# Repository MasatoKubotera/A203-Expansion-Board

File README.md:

<html lang="en">

<head>
    <meta charset="uft-8">
    <meta name="author" content="Masato Kubotera">
    <meta name="description" content="">
</head>

<body>
    <p><strong>This product is currently under development!</strong></p>
    <h1>A203 V2 Expansion Board</h1>
        <p>
            This product is a board that expands the functions of the A203 (Version 2) carrier board manufactured by Seeed Stuido, developed for the SUSTAINA-OP<sup>TM</sup>. Several modules developed for SUSTAINA-OP<sup>TM</sup> can be attached/connected to this board and used by connecting to the Multifunctional Port and USB Port on the carrier board. In addition, the USB 2.0 High Speed(480MHz) 3-Port Hub is installed for further expandability.
        </p>
    <h2>Features Rev. 1</h2>
        <p>
            <table>
                <tr>
                    <th>Top Surface of PCB</th>
                    <th>Bottom Surface of PCB</th>
                    <th>Assembled Electronic Components</th>
                </tr>
                <tr>
                    <td></td>
                    <td></td>
                    <td></td>
                </tr>
            </table>
        </p>
    <h3>PCB</h3>
        <p>
            <ul>
                <li>81.20mm x 46.40mm PCB layout</li>
                The shape of the connector does not interfere with the connectors on the A203 V2.
                <li>Two types of USB-HUB Upstream Ports</li>
                    <ul>
                        <li>0.5mm pitch 20P ZIF Connector</li>
                        Compliant with W11: 20PIN(USB 3.0 ZIF) on the A203 V2.
                        <li>USB Mini-B Connector (Optional)</li>
                    </ul>
                <li>2 x USB 2.0 Type-A USB-HUB Downstream Ports</li>
                <li>1 x <a href="https://github.com/SUSTAINA-OP/ICM-42688-P-Module">SUSTAINA-OP/ICM-42688-P-Module</a> Attachment Port</li>
                The I/F with A203V2 can be selected from the following using the shortlands on the product.
                <ul>
                    <li>SPI </li>
                    <li>I2C: Selectable slave address 0x68/0x69</li>
                </ul>
                <li>1 x <a href="https://github.com/SUSTAINA-OP/USB-to-Quad-RS-485-Conv-Module">SUSTAINA-OP/USB-to-Quad-RS-485-Conv-Module</a> Attachment Port</li>
                <li>14 x LED Indicators</li>
                <li>
                    1 x Port for Connection to <a href="https://github.com/SUSTAINA-OP/SUSTAINA-Core-Board">SUSTAINA-OP/SUSTAINA-Core-Board</a>
                    <ul>
                        <li>2 x 7 Pin Flat Cable Connector (MIL Standard Connector)
                            <ul>
                                <li><strong>2 x 3V3</strong>: 3.3 V Power Supply</li>
                                <li><strong>SCL</strong>: I2C Serial Clock</li>
                                <li><strong>SDA</strong>: I2C Serial Data</li>
                                <li><strong>A-DP</strong>: RS-485 Data Signal Plus of CH-A</li>
                                <li><strong>A-DM</strong>: RS-485 Data Signal Minus of CH-A</li>
                                <li><strong>B-DP</strong>: RS-485 Data Signal Plus of CH-B</li>
                                <li><strong>B-DM</strong>: RS-485 Data Signal Minus of CH-B</li>
                                <li><strong>C-DP</strong>: RS-485 Data Signal Plus of CH-C</li>
                                <li><strong>C-DM</strong>: RS-485 Data Signal Minus of CH-C</li>
                                <li><strong>D-DP</strong>: RS-485 Data Signal Plus of CH-D</li>
                                <li><strong>D-DM</strong>: RS-485 Data Signal Minus of CH-D</li>
                                <li><strong>2 x GND</strong>: Common Ground</li>
                            </ul>
                        </li>
                    </ul>
                </li>
            </ul>
        </p>
    <h2>Development Environments</h2>
    <p>
        This product is designed with the following software.
            <ul>
                <li><a href="https://www.autodesk.com/products/eagle/overview">Autodesk Eagle 9.6.2</a></li>
            </ul>
    </p>
    <h2>Repository Contents</h2>
        <p>
            <dl>
                <dt><a href="/images">\images</a></dt>
                <dd>PCB preview images and capture of design screen</dd>
                <dt><a href="/libraries">\libraries</a></dt>
                <dd>Libraries used in Autodesk Eagle design</dd>
                <dt><a href="/pcb_order">\pcb_order</a> </dt>
                <dd>Gerber data and documentation for ordering PCB</dd>
                <dt><a href="/schematic.pdf">schematic.pdf</a></dt>
                <dd>Circuit diagram of this product</dd>
                <dt>*.brd</dt>
                <dd>Board wiring design file by Autodesk Eagle</dd>
                <dt>*.sch</dt>
                <dd>Circuit diagram design file by Autodesk Eagle</dd>
                <dt><a href="/.gitignore">.gitignore</a></dt>
                <dd>A file that tells Git not to track a particular file</dd>            <dt><a href="/LICENSE">LICENSE</a></dt>
                <dd>License to use this product</dd>
            </dl>
        </p>
    <h2>Documentation</h2>
        <p>
            The following documents are available for this product.
            <ul>
                <li><a href="/pcb_order/README.md">\pcb_order\README.md</a>: Information for ordering the PCB or PCBA</li>
            </ul>
        </p>
    <h2>References</h2>
        
    <h2>Contact</h2>
        <p>
            If you have any questions, please contact the designer of this product, Masato Kubodera, by <a href="mailto:masato.kubotera@sustaina-op.com">e-mail</a>.<br>
            E-mail: <a href="mailto:masato.kubotera@sustaina-op.com">masato.kubotera@sustaina-op.com</a>
        </p>
    <h2>License Information</h2>
        <p>
            This product is open source. Please review the <a href="/LICENSE">LICENSE</a> for license information.<br>
            <br>
            This product by Masato Kubotera is licensed under a <a href="http://creativecommons.org/licenses/by-nc-sa/4.0/">Creative Commons Attribution-NonCommercial-ShareAlike 4.0 International License</a>.
        </p>
</body>
</html>

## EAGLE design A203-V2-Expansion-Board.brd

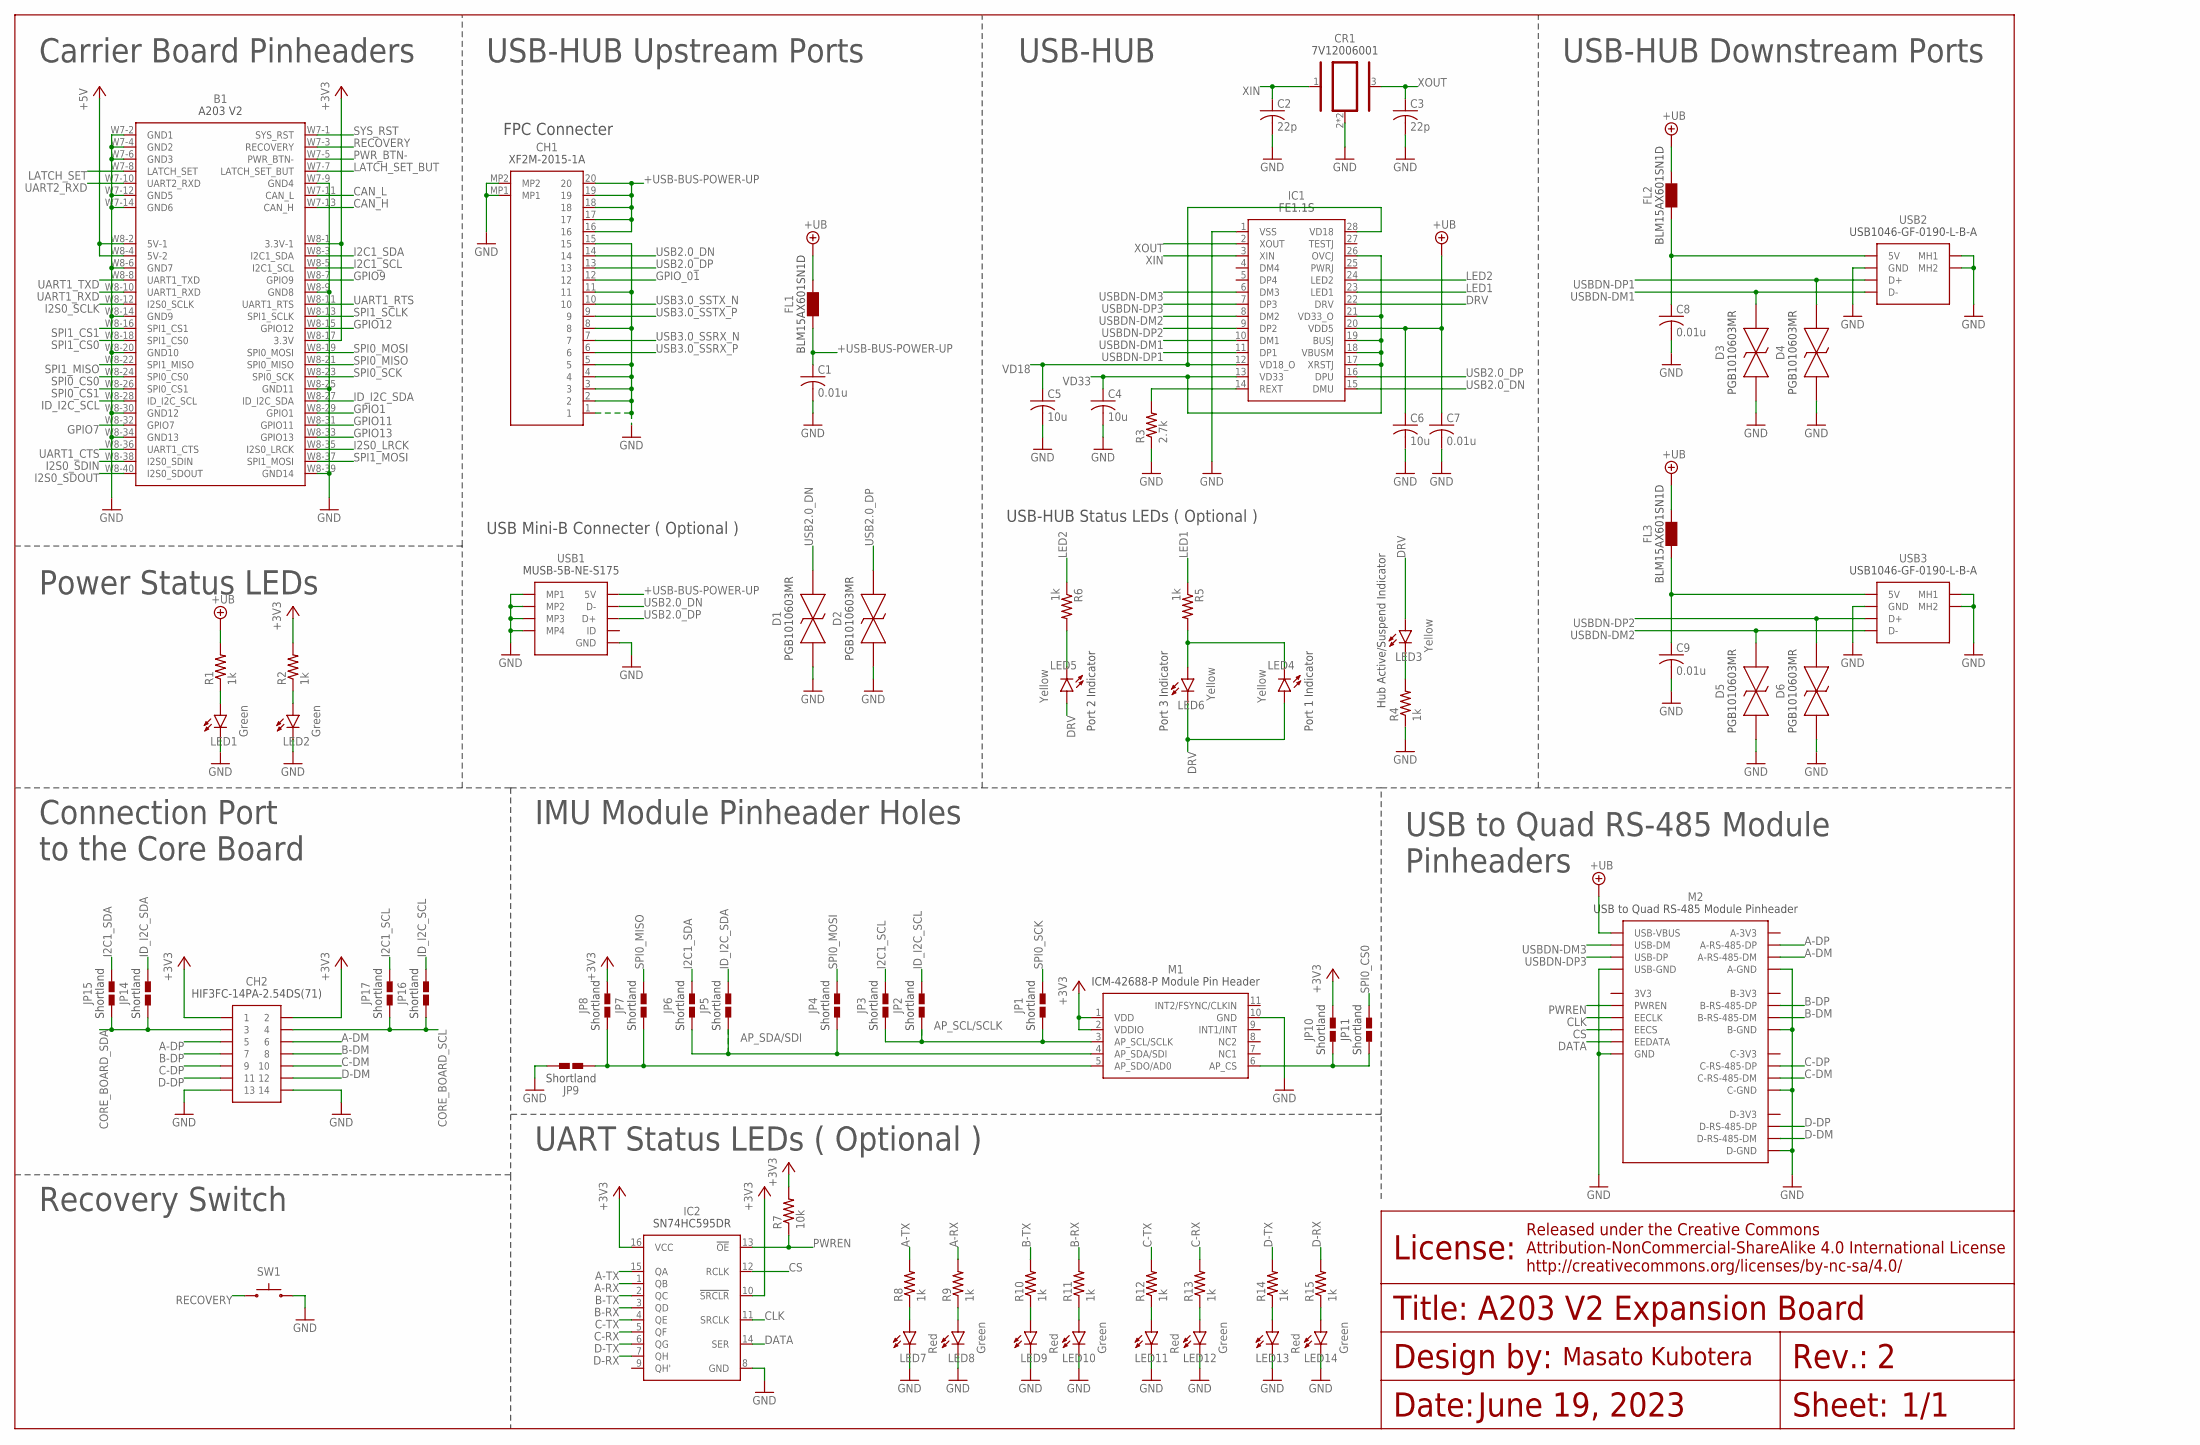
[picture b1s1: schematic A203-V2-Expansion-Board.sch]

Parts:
B1: SEEED_A207_V2; SEEED_A203_V2
C1, C7, C8, C9: 0.01u; C0603
C2, C3: 22p; C0603
C4, C5, C6: 10u; C0603
CH1: XF2M-2015-1A
CH2: HIF3FC-14PA-2.54DS(71)
CR1: 7V12006001
D1, D2, D3, D4, D5, D6: PGB1010603MR; 0603
FL1, FL2, FL3: BLM15AX601SN1D
IC1: FE1.1S
IC2: SN74HC595DR; SOIC-16
JP1, JP2, JP3, JP4, JP5, JP6, JP7, JP8, JP9, JP10, JP11, JP14, JP15, JP16, JP17: SHORTLAND
LED1, LED2, LED8, LED10, LED12, LED14: Green; SML0603
LED3, LED4, LED5, LED6: Yellow; SML0603
LED7, LED9, LED11, LED13: Red; SML0603
M1: ICM-42688-P-MODULE-PINHEADER
M2: USB-TO-QUAD-RS-485-CONV-MODULET-PLACE; USB-TO-QUAD-RS-485-CONV-MODULE-SILK
R1, R2, R4, R5, R6, R8, R9, R10, R11, R12, R13, R14, R15: 1k; R0603
R3: 2.7k; R0603
R7: 10k; R0603
SW1: SKRPACE010
USB1: MINI_USB_B_SMD
USB2, USB3: USB_A_X1_SMD

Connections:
+3V3: B1.W8-1 (3.3V-1), B1.W8-17 (3.3V), CH2.1, CH2.2, IC2.10 (!SRCLR), IC2.16 (VCC), JP8.2, JP10.2, M1.1 (VDD), M1.2 (VDDIO), R2.2, R7.2
+5V: B1.W8-2 (5V-1), B1.W8-4 (5V-2)
+UB: C6.1, C7.1, FL1.2, FL2.2, FL3.2, IC1.20 (VDD5), M2.USB-VBUS, R1.2
+USB-BUS-POWER-UP: C1.1, CH1.16, CH1.17, CH1.18, CH1.19, CH1.20, FL1.1, USB1.1 (5V)
+USB-BUS-POWER_DN1: C8.1, FL2.1, USB2.1 (5V)
+USB-BUS-POWER_DN2: C9.1, FL3.1, USB3.1 (5V)
A-DM: CH2.6, M2.A-RS-485-DM
A-DP: CH2.5, M2.A-RS-485-DP
A-RX: IC2.1 (QB), R9.2
A-TX: IC2.15 (QA), R8.2
AP_CS: JP10.1, JP11.1, M1.6 (AP_CS)
AP_SCL/SCLK: JP1.1, JP2.1, JP3.1, M1.3 (AP_SCL/SCLK)
AP_SDA/SDI: JP4.1, JP5.1, JP6.1, M1.4 (AP_SDA/SDI)
AP_SDO/ADO: JP7.1, JP8.1, JP9.1, M1.5 (AP_SDO/AD0)
B-DM: CH2.8, M2.B-RS-485-DM
B-DP: CH2.7, M2.B-RS-485-DP
B-RX: IC2.3 (QD), R11.2
B-TX: IC2.2 (QC), R10.2
C-DM: CH2.10, M2.C-RS-485-DM
C-DP: CH2.9, M2.C-RS-485-DP
C-RX: IC2.5 (QF), R13.2
C-TX: IC2.4 (QE), R12.2
CAN_H: B1.W7-13 (CAN_H)
CAN_L: B1.W7-11 (CAN_L)
CLK: IC2.11 (SRCLK), M2.EECLK
CORE_BOARD_SCL: CH2.4, JP16.1, JP17.1
CORE_BOARD_SDA: CH2.3, JP14.1, JP15.1
CS: IC2.12 (RCLK), M2.EECS
D-DM: CH2.12, M2.D-RS-485-DM
D-DP: CH2.11, M2.D-RS-485-DP
D-RX: IC2.7 (QH), R15.2
D-TX: IC2.6 (QG), R14.2
DATA: IC2.14 (SER), M2.EEDATA
DRV: IC1.22 (DRV), LED3.A, LED4.A, LED5.A, LED6.C
GND: B1.W7-2 (GND1), B1.W7-4 (GND2), B1.W7-6 (GND3), B1.W7-9 (GND4), B1.W7-12 (GND5), B1.W7-14 (GND6), B1.W8-6 (GND7), B1.W8-9 (GND8), B1.W8-14 (GND9), B1.W8-20 (GND10), B1.W8-25 (GND11), B1.W8-30 (GND12), B1.W8-34 (GND13), B1.W8-39 (GND14), C1.2, C2.2, C3.2, C4.2, C5.2, C6.2, C7.2, C8.2, C9.2, CH1.1, CH1.2, CH1.3, CH1.4, CH1.5, CH1.8, CH1.11, CH1.15, CH1.MP1, CH1.MP2, CH2.13, CH2.14, CR1.2, CR1.4, D1.1, D2.1, D3.1, D4.1, D5.1, D6.1, IC1.1 (VSS), IC2.8 (GND), JP9.2, LED1.C, LED2.C, LED7.C, LED8.C, LED9.C, LED10.C, LED11.C, LED12.C, LED13.C, LED14.C, M1.10 (GND), M2.A-GND, M2.B-GND, M2.C-GND, M2.D-GND, M2.GND1 (GND), M2.USB-GND, R3.1, R4.1, SW1.3 (2), SW1.4 (2), USB1.5 (GND), USB1.MP1, USB1.MP2, USB1.MP3, USB1.MP4, USB2.4 (GND), USB2.MH1, USB2.MH2, USB3.4 (GND), USB3.MH1, USB3.MH2
GPIO1: B1.W8-29 (GPIO1)
GPIO7: B1.W8-32 (GPIO7)
GPIO9: B1.W8-7 (GPIO9)
GPIO11: B1.W8-31 (GPIO11)
GPIO12: B1.W8-15 (GPIO12)
GPIO13: B1.W8-33 (GPIO13)
GPIO_01: CH1.12
I2C1_SCL: B1.W8-5 (I2C1_SCL), JP3.2, JP17.2
I2C1_SDA: B1.W8-3 (I2C1_SDA), JP6.2, JP15.2
I2S0_LRCK: B1.W8-35 (I2S0_LRCK)
I2S0_SCLK: B1.W8-12 (I2S0_SCLK)
I2S0_SDIN: B1.W8-38 (I2S0_SDIN)
I2S0_SDOUT: B1.W8-40 (I2S0_SDOUT)
ID_I2C_SCL: B1.W8-28 (ID_I2C_SCL), JP2.2, JP16.2
ID_I2C_SDA: B1.W8-27 (ID_I2C_SDA), JP5.2, JP14.2
LATCH_SET: B1.W7-8 (LATCH_SET)
LATCH_SET_BUT: B1.W7-7 (LATCH_SET_BUT)
LED1: IC1.23 (LED1), R5.1
LED2: IC1.24 (LED2), R6.1
LED-3V3: LED2.A, R2.1
LED-A-RX: LED8.A, R9.1
LED-A-TX: LED7.A, R8.1
LED-B-RX: LED10.A, R11.1
LED-B-TX: LED9.A, R10.1
LED-C-RX: LED12.A, R13.1
LED-C-TX: LED11.A, R12.1
LED-D-RX: LED14.A, R15.1
LED-D-TX: LED13.A, R14.1
LED-FE1.1S-DRV: LED3.C, R4.2
LED-FE1.1S-INDIVATOR1: LED4.C, LED6.A, R5.2
LED-FE1.1S-INDIVATOR2: LED5.C, R6.2
LED-UB: LED1.A, R1.1
PWREN: IC2.13 (!OE), M2.PWREN, R7.1
PWR_BTN-: B1.W7-5 (PWR_BTN-)
RECOVERY: B1.W7-3 (RECOVERY), SW1.1, SW1.2 (1)
REXT_FE1.1S: IC1.14 (REXT), R3.2
SPI0_CS0: B1.W8-24 (SPI0_CS0), JP11.2
SPI0_CS1: B1.W8-26 (SPI0_CS1)
SPI0_MISO: B1.W8-21 (SPI0_MISO), JP7.2
SPI0_MOSI: B1.W8-19 (SPI0_MOSI), JP4.2
SPI0_SCK: B1.W8-23 (SPI0_SCK), JP1.2
SPI1_CS0: B1.W8-18 (SPI1_CS0)
SPI1_CS1: B1.W8-16 (SPI1_CS1)
SPI1_MISO: B1.W8-22 (SPI1_MISO)
SPI1_MOSI: B1.W8-37 (SPI1_MOSI)
SPI1_SCLK: B1.W8-13 (SPI1_SCLK)
SYS_RST: B1.W7-1 (SYS_RST)
UART1_CTS: B1.W8-36 (UART1_CTS)
UART1_RTS: B1.W8-11 (UART1_RTS)
UART1_RXD: B1.W8-10 (UART1_RXD)
UART1_TXD: B1.W8-8 (UART1_TXD)
UART2_RXD: B1.W7-10 (UART2_RXD)
USB2.0_DN: CH1.14, D1.2, IC1.15 (DMU), USB1.2 (D-)
USB2.0_DP: CH1.13, D2.2, IC1.16 (DPU), USB1.3 (D+)
USB3.0_SSRX_N: CH1.7
USB3.0_SSRX_P: CH1.6
USB3.0_SSTX_N: CH1.10
USB3.0_SSTX_P: CH1.9
USBDN-DM1: D3.2, IC1.10 (DM1), USB2.2 (D-)
USBDN-DM2: D5.2, IC1.8 (DM2), USB3.2 (D-)
USBDN-DM3: IC1.6 (DM3), M2.USB-DM
USBDN-DP1: D4.2, IC1.11 (DP1), USB2.3 (D+)
USBDN-DP2: D6.2, IC1.9 (DP2), USB3.3 (D+)
USBDN-DP3: IC1.7 (DP3), M2.USB-DP
VD18: C5.1, IC1.12 (VD18_O), IC1.28 (VD18)
VD33: C4.1, IC1.13 (VD33), IC1.17 (XRSTJ), IC1.18 (VBUSM), IC1.19 (BUSJ), IC1.21 (VD33_O), IC1.26 (OVCJ)
XIN: C2.1, CR1.1, IC1.3 (XIN)
XOUT: C3.1, CR1.3, IC1.2 (XOUT)

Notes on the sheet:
Carrier Board Pinheaders
Power Status LEDs
UART Status LEDs ( Optional )
IMU Module Pinheader Holes
USB to Quad RS-485 Module Pinheaders
USB-HUB Upstream Ports
Connection Port to the Core Board
USB-HUB Downstream Ports
USB-HUB
1/1
June 19, 2023
A203 V2 Expansion Board
Hub Active/Suspend Indicator
Port 1 Indicator
Port 2 Indicator
Port 3 Indicator
USB Mini-B Connecter ( Optional )
FPC Connecter
USB-HUB Status LEDs ( Optional )
Recovery Switch

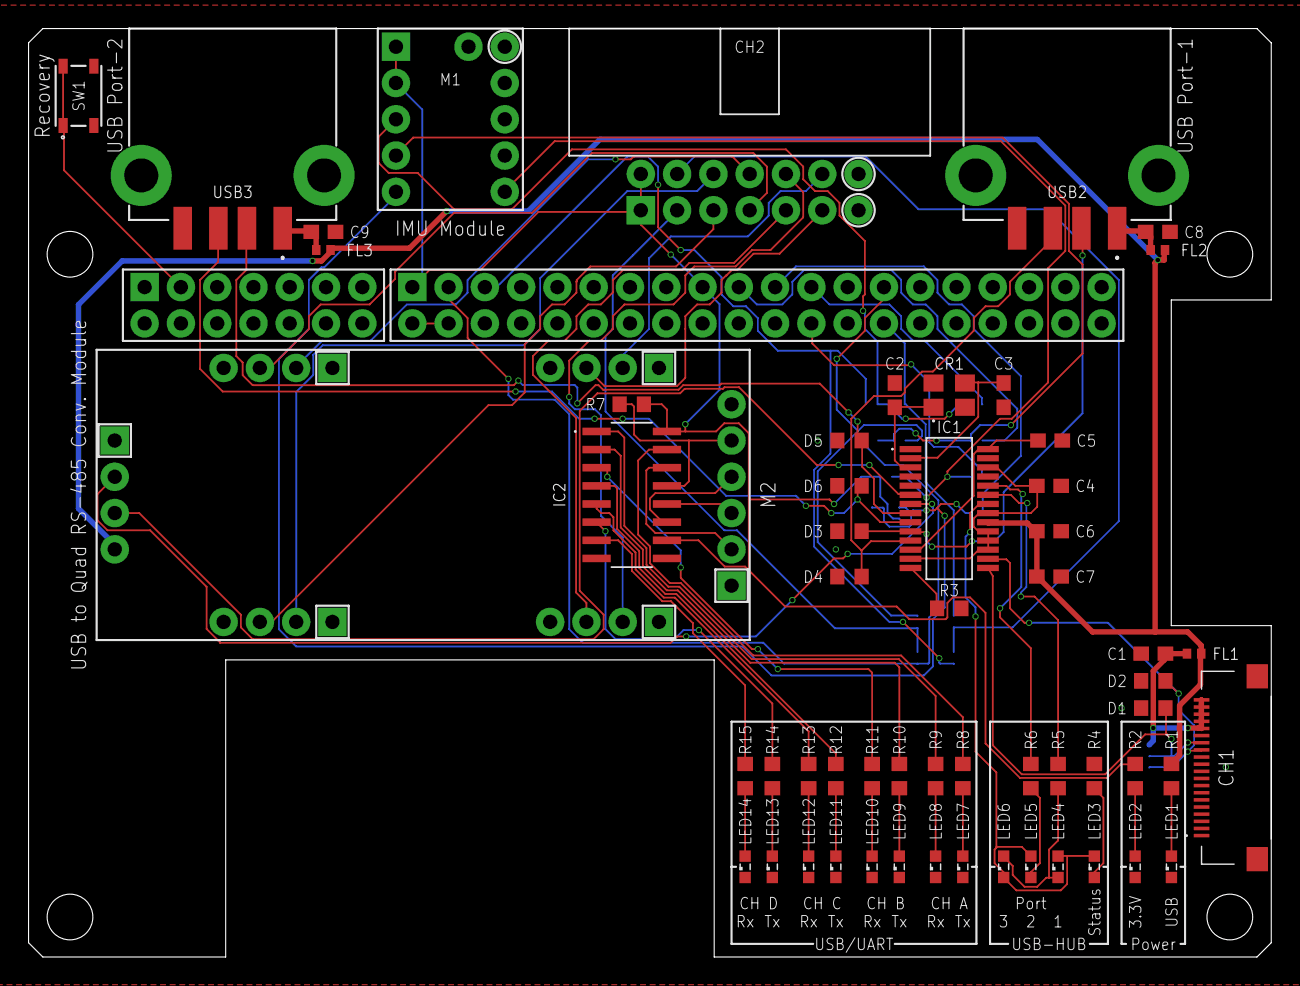
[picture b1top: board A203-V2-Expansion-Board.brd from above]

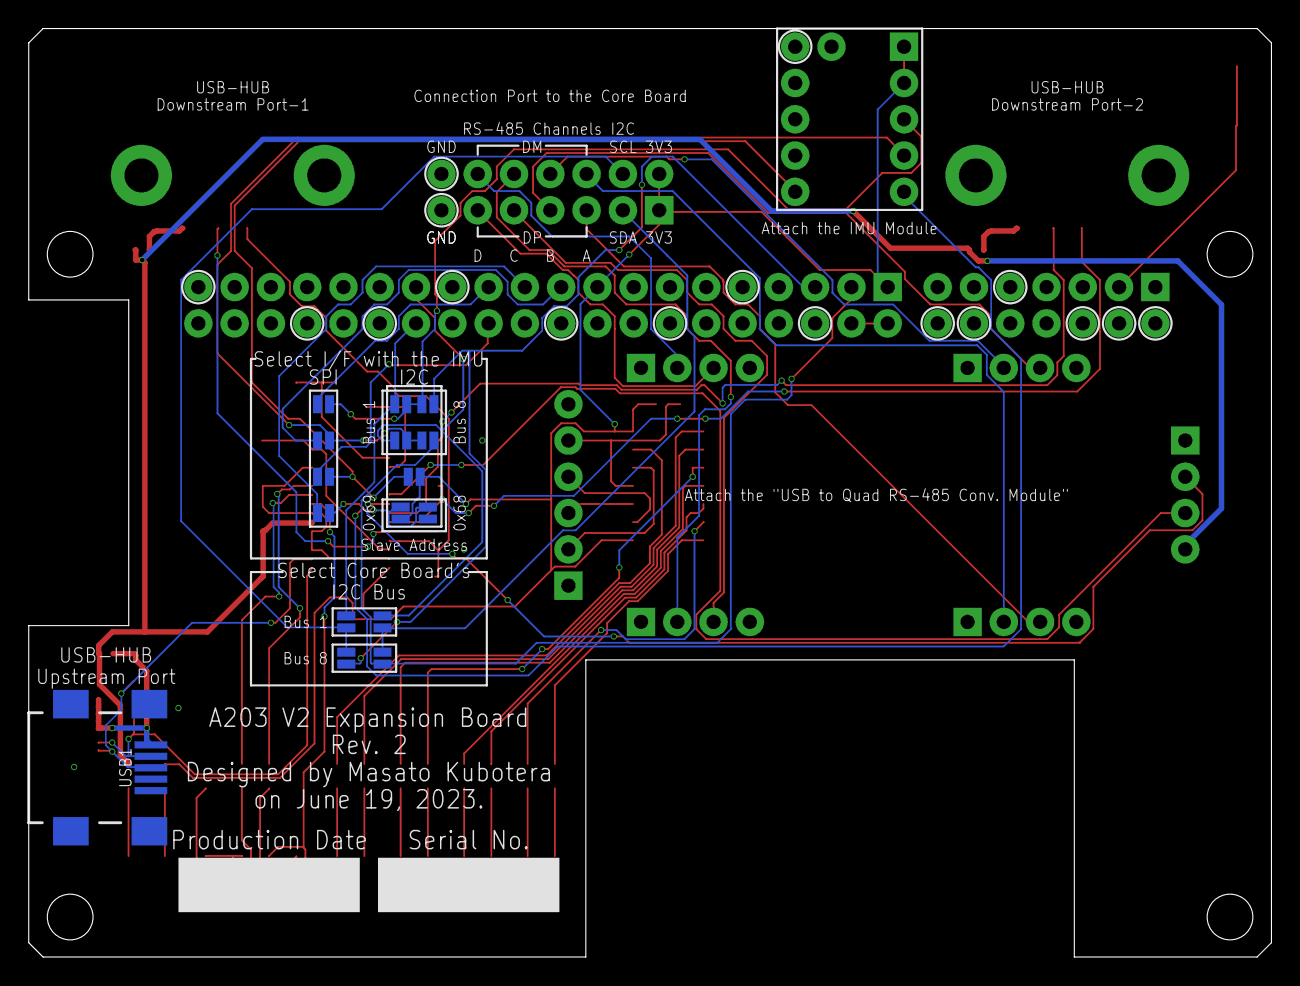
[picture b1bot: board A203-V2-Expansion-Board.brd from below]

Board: 2 copper layers, 87.0 x 65.0 mm, 74 parts (16 on the bottom side), 71 nets.

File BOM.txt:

Qty Value                                 Device                                Package                             Parts                                                                           Description                
4   0.01u                                 C-USC0603                             C0603                               C1, C7, C8, C9                                                                  CAPACITOR, American symbol 
1   10k                                   R-US_R0603                            R0603                               R7                                                                              RESISTOR, American symbol  
3   10u                                   C-USC0603                             C0603                               C4, C5, C6                                                                      CAPACITOR, American symbol 
13  1k                                    R-US_R0603                            R0603                               R1, R2, R4, R5, R6, R8, R9, R10, R11, R12, R13, R14, R15                        RESISTOR, American symbol  
1   2.7k                                  R-US_R0603                            R0603                               R3                                                                              RESISTOR, American symbol  
2   22p                                   C-USC0603                             C0603                               C2, C3                                                                          CAPACITOR, American symbol 
1   7V12006001                            7V12006001                            7V12006001                          CR1                                                                                                        
3   BLM15AX601SN1D                        BLM15AX601SN1D                        BLM15AX601SN1D                      FL1, FL2, FL3                                                                                              
1   FE1.1S                                FE1.1S                                FE1.1S                              IC1                                                                                                        
6   Green                                 LEDSML0603                            SML0603                             LED1, LED2, LED8, LED10, LED12, LED14                                           LED                        
1   HIF3FC-14PA-2.54DS(71)                HIF3FC-14PA-2.54DS(71)                HIF3FC-14PA-2.54DS(71)              CH2                                                                                                        
1   ICM-42688-P-MODULE-PINHEADER          ICM-42688-P-MODULE-PINHEADER          ICM-42688-P-MODULE-PINHEADER        M1                                                                                                         
1   MINI_USB_B_SMD                        MINI_USB_B_SMD                        MINI_USB_B_SMD                      USB1                                                                                                       
6   PGB1010603MR                          PGB1010603MR                          0603                                D1, D2, D3, D4, D5, D6                                                                                     
4   Red                                   LEDSML0603                            SML0603                             LED7, LED9, LED11, LED13                                                        LED                        
1   SEEED_A207_V2                         SEEED_A207_V2                         SEEED_A203_V2                       B1                                                                                                         
15  SHORTLAND                             SHORTLAND                             SHORTLAND                           JP1, JP2, JP3, JP4, JP5, JP6, JP7, JP8, JP9, JP10, JP11, JP14, JP15, JP16, JP17                            
1   SKRPACE010                            SKRPACE010                            SKRPACE010                          SW1                                                                                                        
1   SN74HC595DR                           SN74HC595DR                           SOIC-16                             IC2                                                                                                        
1   USB-TO-QUAD-RS-485-CONV-MODULET-PLACE USB-TO-QUAD-RS-485-CONV-MODULET-PLACE USB-TO-QUAD-RS-485-CONV-MODULE-SILK M2                                                                                                         
2   USB_A_X1_SMD                          USB_A_X1_SMD                          USB_A_X1_SMD                        USB2, USB3                                                                                                 
1   XF2M-2015-1A                          XF2M-2015-1A                          XF2M-2015-1A                        CH1                                                                                                        
4   Yellow                                LEDSML0603                            SML0603                             LED3, LED4, LED5, LED6                                                          LED

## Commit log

2023-05-21 Initial upload
2023-05-23 Fixed silk printing
2023-05-23 Update files for PCBA
2023-05-23 Change the part number
2023-05-23 Update README.md for PCBA
2023-05-23 Update PCB images
2023-05-23 Add LICENSE
2023-05-31 Fixed wiring error on USB DN Port 3
2023-06-02 Update README.md for pcb order
2023-06-14 Change default display settings
2023-06-20 Create Rev. 2

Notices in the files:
parts and their libraries:
Frames: Released under the Creative Commons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
